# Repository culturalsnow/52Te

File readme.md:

# 52Te

52Te is a split keyboard inspired by the NISSE keyboard created by Esrille.

https://www.esrille.com/keyboard/

The firmware is heavily based on Lily58 due to wiring and layout similarities.

https://github.com/kata0510/Lily58

Right now this is hand-wired with ProMicroSocket and BitBoard by swanmatch.

https://github.com/swanmatch/MxLEDBitPCB

May add a PCB for v2.0.

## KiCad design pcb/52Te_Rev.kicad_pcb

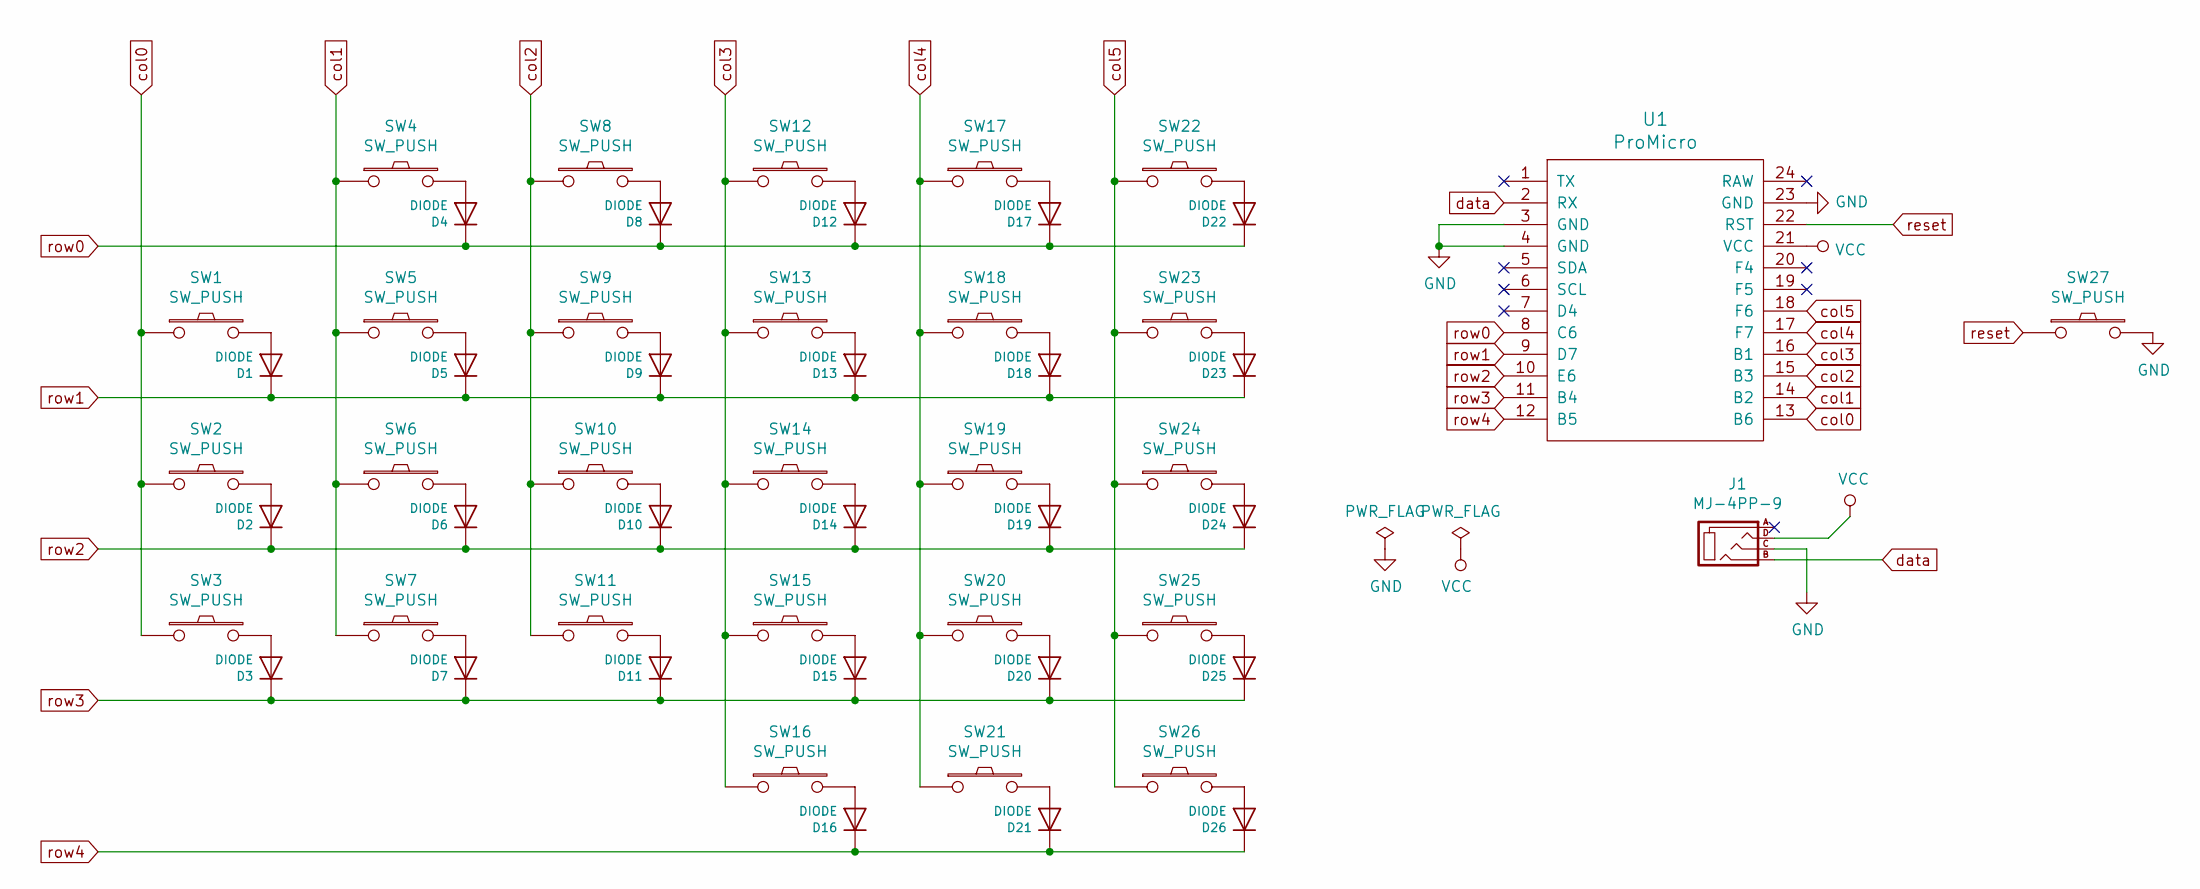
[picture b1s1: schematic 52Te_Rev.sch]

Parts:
D1, D2, D3, D4, D5, D6, D7, D8, D9, D10, D11, D12, D13, D14, D15, D16, D17, D18, D19, D20, D21, D22, D23, D24, D25, D26: DIODE; D3_TH_SMD
J1: MJ-4PP-9
SW1, SW2, SW3, SW4, SW5, SW6, SW7, SW8, SW9, SW10, SW11, SW12, SW13, SW14, SW15, SW16, SW17, SW18, SW19, SW20, SW21, SW22, SW23, SW24, SW25, SW26: SW_PUSH; CherryMX_Hotswap
SW27: SW_PUSH; ResetSW
U1: ProMicro; ProMicro_v2

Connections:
GND: J1.C, SW27.2, U1.3 (GND), U1.4 (GND), U1.23 (GND)
unnamed: D1.2 (A), SW1.2
unnamed: D2.2 (A), SW2.2
unnamed: D3.2 (A), SW3.2
unnamed: D4.2 (A), SW4.2
unnamed: D5.2 (A), SW5.2
unnamed: D6.2 (A), SW6.2
unnamed: D7.2 (A), SW7.2
unnamed: D8.2 (A), SW8.2
unnamed: D9.2 (A), SW9.2
unnamed: D10.2 (A), SW10.2
unnamed: D11.2 (A), SW11.2
unnamed: D12.2 (A), SW12.2
unnamed: D13.2 (A), SW13.2
unnamed: D14.2 (A), SW14.2
unnamed: D15.2 (A), SW15.2
unnamed: D16.2 (A), SW16.2
unnamed: D17.2 (A), SW17.2
unnamed: D18.2 (A), SW18.2
unnamed: D19.2 (A), SW19.2
unnamed: D20.2 (A), SW20.2
unnamed: D21.2 (A), SW21.2
unnamed: D22.2 (A), SW22.2
unnamed: D23.2 (A), SW23.2
unnamed: D24.2 (A), SW24.2
unnamed: D25.2 (A), SW25.2
unnamed: D26.2 (A), SW26.2
SCL: U1.6 (SCL)
SDA: U1.5 (SDA)
VCC: J1.D, U1.21 (VCC)
col0: SW1.1, SW2.1, SW3.1, U1.13 (B6)
col1: SW4.1, SW5.1, SW6.1, SW7.1, U1.14 (B2)
col2: SW8.1, SW9.1, SW10.1, SW11.1, U1.15 (B3)
col3: SW12.1, SW13.1, SW14.1, SW15.1, SW16.1, U1.16 (B1)
col4: SW17.1, SW18.1, SW19.1, SW20.1, SW21.1, U1.17 (F7)
col5: SW22.1, SW23.1, SW24.1, SW25.1, SW26.1, U1.18 (F6)
data: J1.B, U1.2 (RX)
reset: SW27.1, U1.22 (RST)
row0: D4.1 (K), D8.1 (K), D12.1 (K), D17.1 (K), D22.1 (K), U1.8 (C6)
row1: D1.1 (K), D5.1 (K), D9.1 (K), D13.1 (K), D18.1 (K), D23.1 (K), U1.9 (D7)
row2: D2.1 (K), D6.1 (K), D10.1 (K), D14.1 (K), D19.1 (K), D24.1 (K), U1.10 (E6)
row3: D3.1 (K), D7.1 (K), D11.1 (K), D15.1 (K), D20.1 (K), D25.1 (K), U1.11 (B4)
row4: D16.1 (K), D21.1 (K), D26.1 (K), U1.12 (B5)

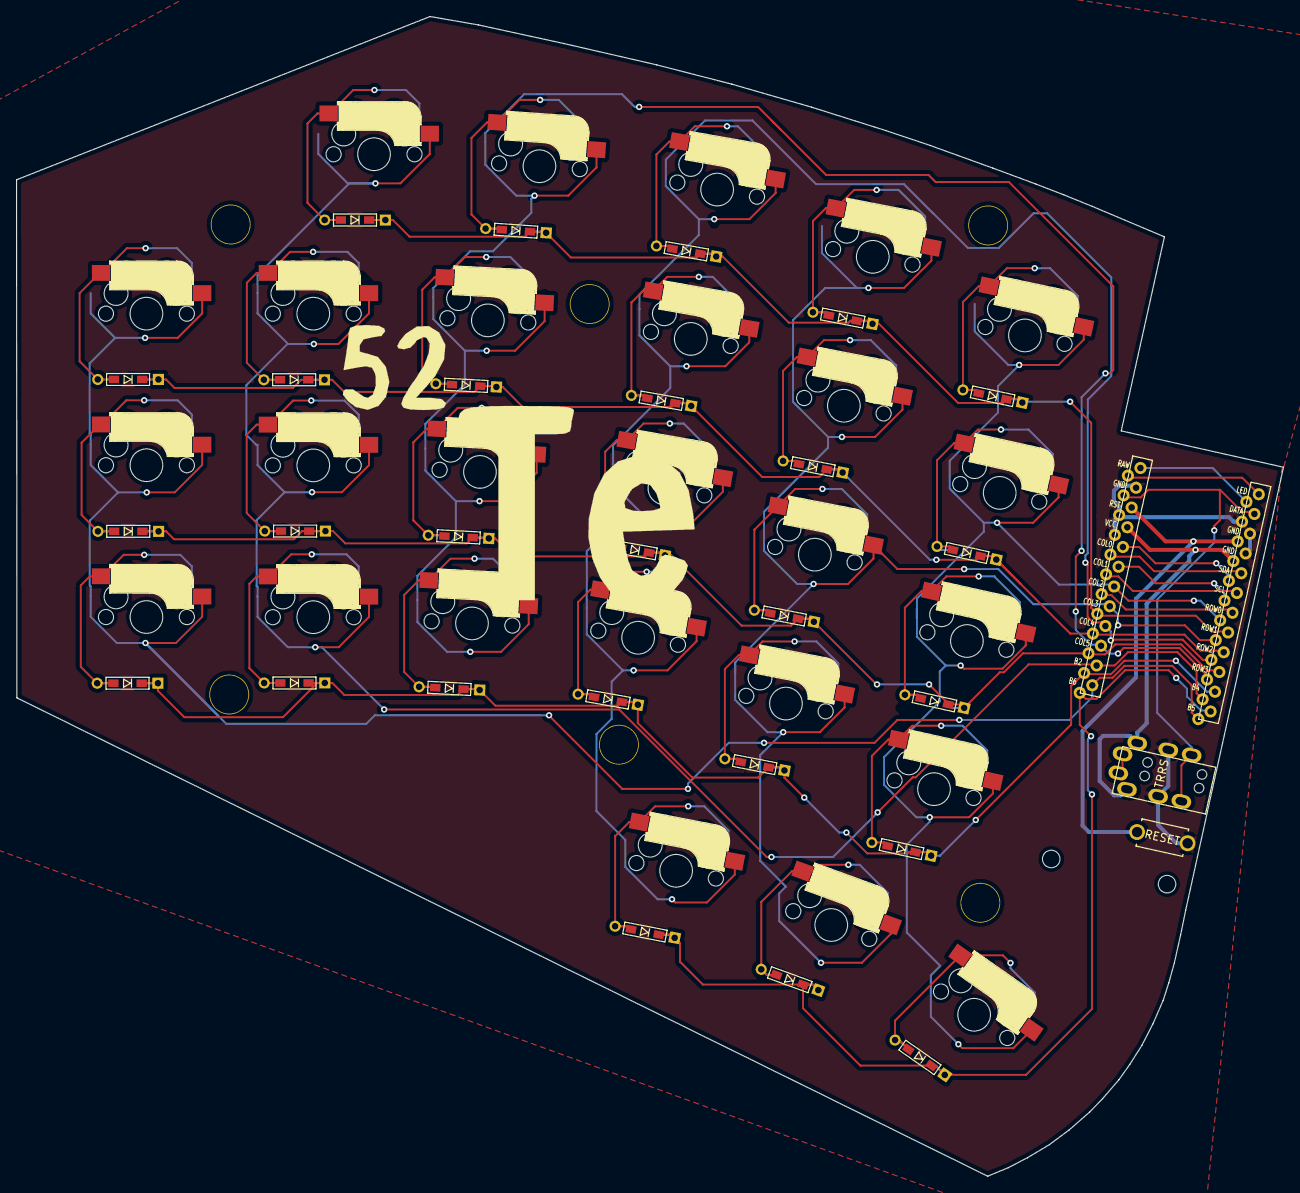
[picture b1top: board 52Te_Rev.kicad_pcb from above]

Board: 2 copper layers, 159.1 x 145.6 mm, 61 parts (0 on the bottom side), 41 nets.

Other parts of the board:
Ref**: Val**; HOLE
Ref**#2, Ref**#3, Ref**#4, Ref**#5, Ref**#6: Val**; HOLE

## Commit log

2018-12-26 added Lily58 link
2018-12-29 changes 20181229
2018-12-31 20181231
2019-01-04 20190104
2019-01-06 keymap updated
2019-01-21 added PCB file for left hand
2019-01-21 plate bulder dxf
2019-01-21 EOD 20190121 at work
2019-01-21 20190122 placement
2019-01-22 first draft pcb lefthand
2019-01-24 new pcb reversible design
2019-01-24 v1.0 final 20190124
2019-01-28 firmware update for pcb
2019-01-31 redo pcb
2019-01-31 20190131
2019-02-01 latest 20190201
2019-02-13 20190213 added logos
2019-02-18 gerber uploaded
2019-03-05 fixed PCB TRRS jack connection
2019-03-05 new gerber file
2019-03-05 added screw holes back, new gerber
2019-03-05 added logos
2019-03-05 removed OLED footprints
2019-03-06 removed some files
2019-03-12 added holes and redid routing around trrs/reset
